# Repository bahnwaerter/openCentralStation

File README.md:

openCentralStation
==================

###**The openCentralStation is a model railway command station project which can control various model railway protocols.**
------------------

**Copyright (C) 2014 Manuel Bentele**

**Without an official permission commercial use is not permitted.**
**Forking this project is not permitted.**  

*This program is free software; you can redistribute it and/or modify it under the terms of the GNU General Public License as published by the Free Software Foundation; either version 2 of the License, or (at your option) any later version.*
  
*This program is distributed in the hope that it will be useful, but WITHOUT ANY WARRANTY; without even the implied warranty of MERCHANTABILITY or FITNESS FOR A PARTICULAR PURPOSE.  See the GNU General Public License for more details.*
  
*You should have received a copy of the GNU General Public License along with this program; if not, write to the Free Software Foundation, Inc., 59 Temple Place - Suite 330, Boston, MA  02111-1307, USA.*

**Project License: GNU General Public License 2**

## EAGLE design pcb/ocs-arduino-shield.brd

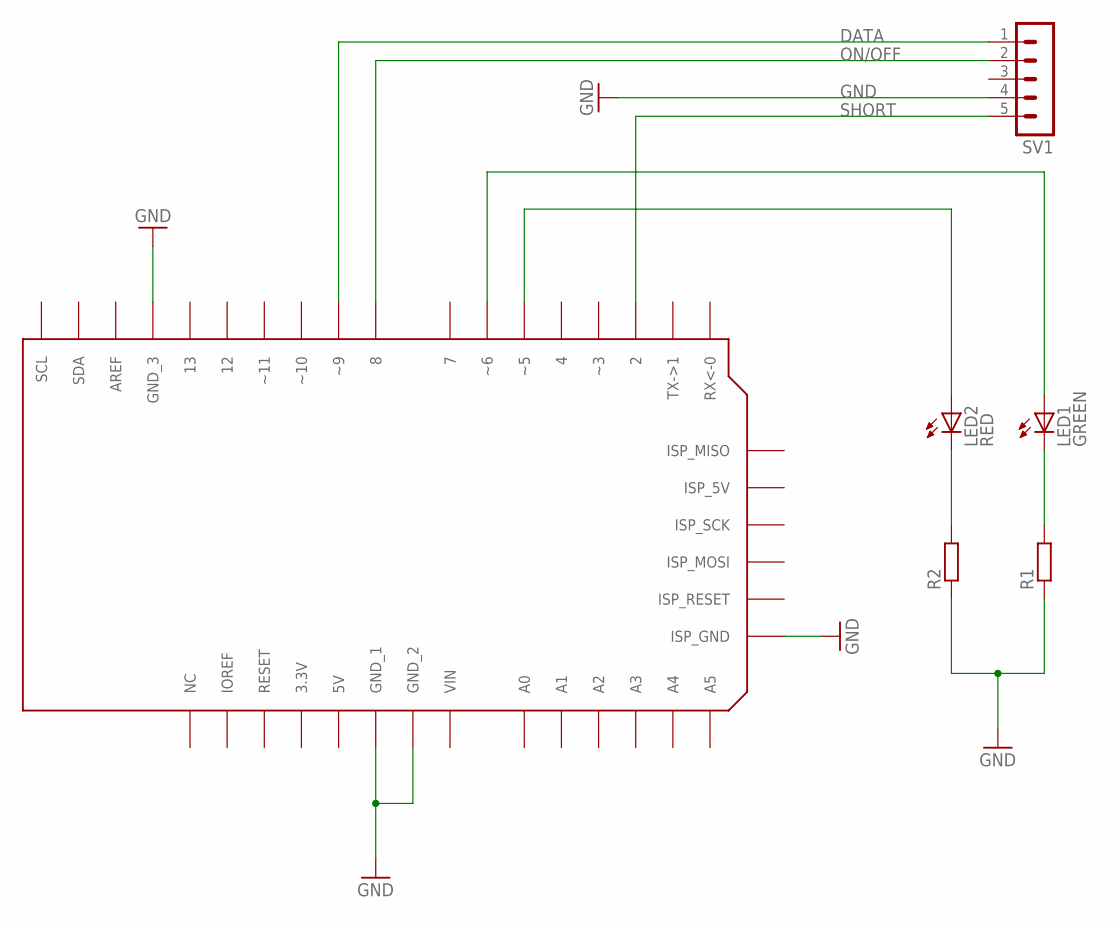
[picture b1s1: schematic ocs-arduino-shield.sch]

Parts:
LED1: GREEN; LED3MM
LED2: RED; LED3MM
R1, R2: R-EU_0207_10; 0207/10
SH1: ARDUINO-UNO-SHIELD
SV1: MA05-1

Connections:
DATA: SH1.~9, SV1.1
GND: R1.1, R2.1, SH1.GND_1, SH1.GND_2, SH1.GND_3, SH1.ISP_GND, SV1.4
unnamed: LED1.A, SH1.~6
unnamed: LED2.A, SH1.~5
unnamed: LED2.K (C), R2.2
unnamed: LED1.K (C), R1.2
ON/OFF: SH1.8, SV1.2
SHORT: SH1.2, SV1.5

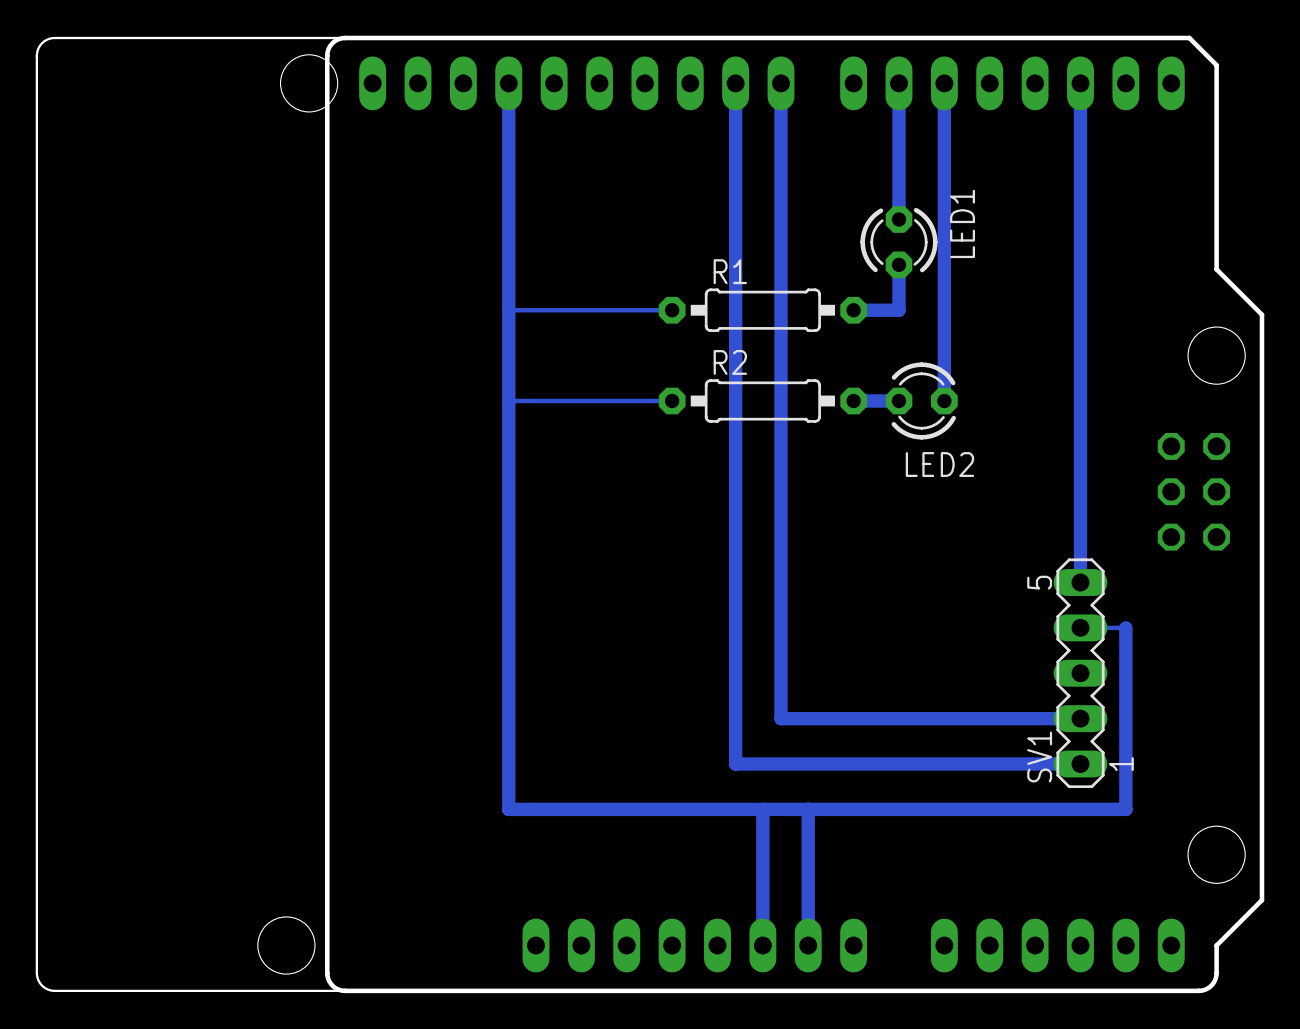
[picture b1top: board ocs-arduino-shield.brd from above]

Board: 2 copper layers, 68.6 x 53.3 mm, 6 parts (0 on the bottom side), 8 nets.

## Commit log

2014-04-18 modified README
2014-04-18 added gitignore file
2014-08-27 created schematic and layout for the ocs-arduino-shield
2014-08-27 added functions to control a booster and detect short circuits
2014-08-27 added uart functions that are based on Peter Fleurys UART library
2014-11-14 added codeblocks project file and a config file
